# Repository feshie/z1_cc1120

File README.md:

z1_cc1120
=========

A Simple board to conect the Z1 node to the CC1120

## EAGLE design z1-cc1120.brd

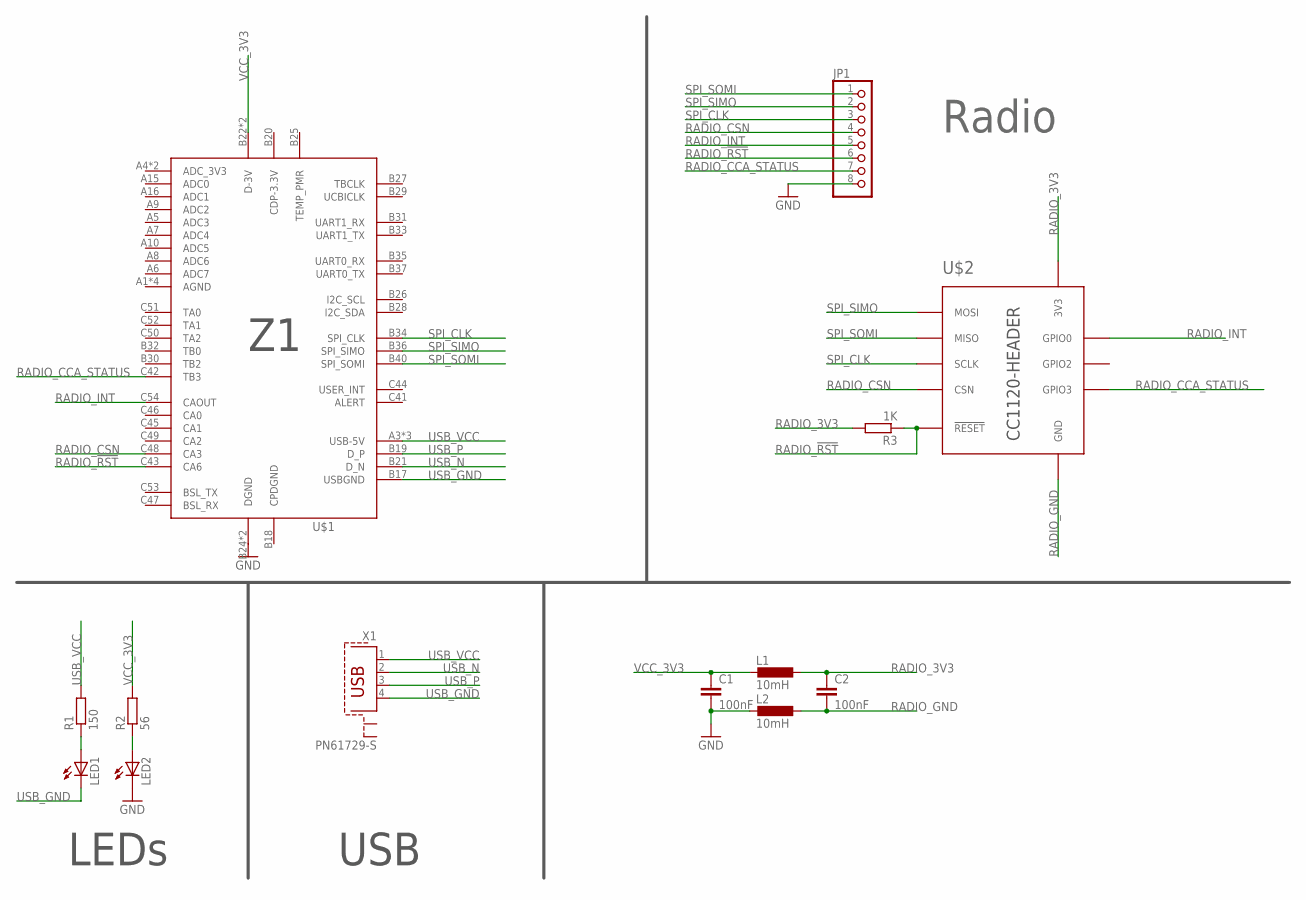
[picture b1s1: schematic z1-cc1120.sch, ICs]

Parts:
C1, C2: 100nF; C0805
JP1: PINHD-1X8; 1X08
L1, L2: 10mH; L3230M
LED1, LED2: LEDCHIP-LED0805; CHIP-LED0805
R1: 150; R0805
R2: 56; R0805
R3: 1K; R0805
U$1: Z1
U$2: CC1120-HEADER-SMT; CC1120-HEADERS-SMT
X1: PN61729-S

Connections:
ADC_3V3: U$1.A4 (ADC_3V3), U$1.A14 (ADC_3V3)
GND: C1.2, JP1.8, L2.2, LED2.C, U$1.B24 (DGND), U$1.C39 (DGND)
unnamed: LED2.A, R2.1
unnamed: LED1.A, R1.1
RADIO_3V3: C2.1, L1.1, R3.2, U$2.3V3-1 (3V3), U$2.3V3-2 (3V3)
RADIO_!RST: JP1.6, R3.1, U$1.C43 (CA6), U$2.RESET (!RESET)
RADIO_CCA_STATUS: JP1.7, U$1.C42 (TB3), U$2.GPIO3
RADIO_CSN: JP1.4, U$1.C48 (CA3), U$2.CSN
RADIO_GND: C2.2, L2.1, U$2.GND, U$2.GND1 (GND), U$2.GND2 (GND)
RADIO_INT: JP1.5, U$1.C54 (CAOUT), U$2.GPIO0
SPI_CLK: JP1.3, U$1.B34 (SPI_CLK), U$2.SCLK
SPI_SIMO: JP1.2, U$1.B36 (SPI_SIMO), U$2.MOSI
SPI_SOMI: JP1.1, U$1.B40 (SPI_SOMI), U$2.MISO
USB_GND: LED1.C, U$1.B17 (USBGND), X1.4
USB_N: U$1.B21 (D_N), X1.2
USB_P: U$1.B19 (D_P), X1.3
USB_VCC: R1.2, U$1.A3 (USB-5V), U$1.A13 (USB-5V), U$1.B23 (USB-5V), X1.1
VCC_3V3: C1.1, L1.2, R2.2, U$1.B22 (D-3V), U$1.C40 (D-3V)

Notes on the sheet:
Radio
USB
LEDs

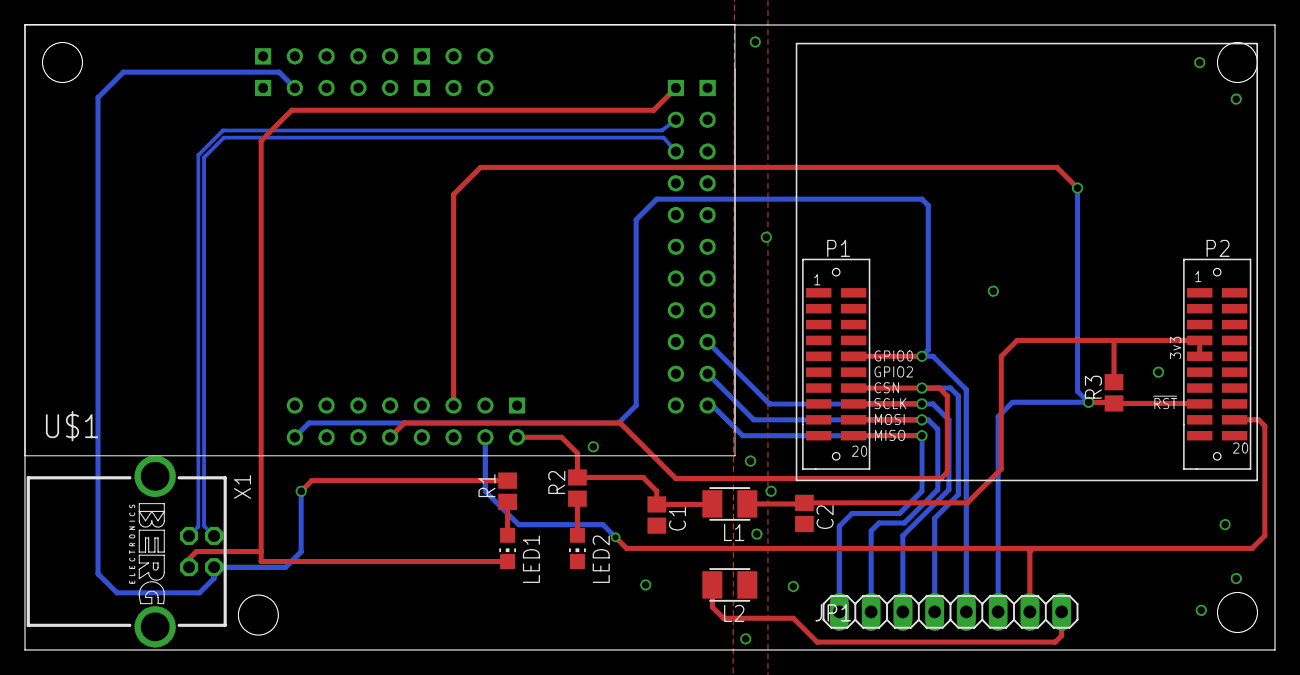
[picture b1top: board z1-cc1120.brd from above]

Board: 2 copper layers, 100.0 x 50.0 mm, 13 parts (0 on the bottom side), 18 nets.

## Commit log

2014-05-10 Initial design of interface board
2014-05-10 Added silk screen info seperated usb_gnd & gnd added mounting holes
2014-05-10 Seperated radio gnd & vcc using inductor/cap network from z1 docs
2014-05-13 added header to ease radio debug
2014-05-13 text moved on silk screen so it's within generated gerber
2014-05-23 !RESET pullup added
2014-05-26 Added reset line from msp to cc1120
2014-05-27 pins now changed to match test rig
2014-05-27 wiring now matches test harness
2014-05-31 added CCA_STATUS
2014-06-01 added !rst and cca status onto debug header
2014-06-16 now very similar length usb tracks
2014-06-23 now set laser width for cutter
